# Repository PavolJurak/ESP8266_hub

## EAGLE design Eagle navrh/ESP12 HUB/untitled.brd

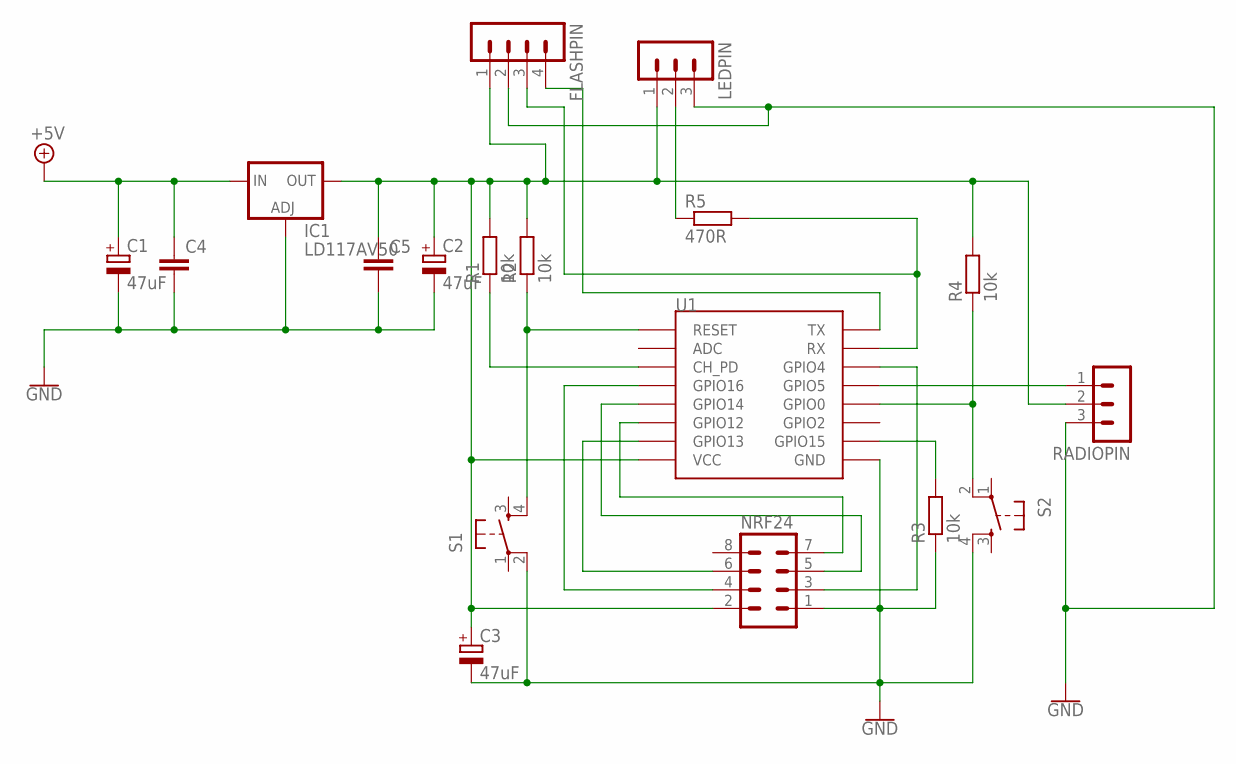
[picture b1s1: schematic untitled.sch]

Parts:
C1, C2, C3: 47uF; E2-5
C4, C5: C-EU025-025X050; C025-025X050
FLASHPIN: MA04-1
IC1: LD117AV50; TO220L1
LEDPIN: MA03-1
NRF24: MA04-2
R1, R2, R3, R4: 10k; 0207/10
R5: 470R; 0207/10
RADIOPIN: MA03-1
S1, S2: TAC_SWITCHPTH; TACTILE-PTH
U1: ESP12

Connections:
GND: C1.-, C2.-, C3.-, C4.2, C5.2, FLASHPIN.2, IC1.1 (ADJ), LEDPIN.3, NRF24.1, R3.1, RADIOPIN.3, S1.2, S2.4, U1.GND
unnamed: NRF24.6, U1.GPIO13
unnamed: R2.1, S1.4, U1.RESET
unnamed: R1.1, U1.CH_PD
unnamed: C2.+, C3.+, C5.1, FLASHPIN.1, IC1.2 (OUT), LEDPIN.1, NRF24.2, R1.2, R2.2, R4.2, RADIOPIN.2, U1.VCC
unnamed: R3.2, U1.GPIO15
unnamed: NRF24.7, U1.GPIO12
unnamed: NRF24.5, U1.GPIO14
unnamed: NRF24.3, U1.GPIO4
unnamed: NRF24.4, U1.GPIO16
unnamed: RADIOPIN.1, U1.GPIO5
unnamed: C1.+, C4.1, IC1.3 (IN)
unnamed: FLASHPIN.3, R5.2, U1.RX
unnamed: R4.1, S2.2, U1.GPIO0
unnamed: LEDPIN.2, R5.1
unnamed: FLASHPIN.4, U1.TX

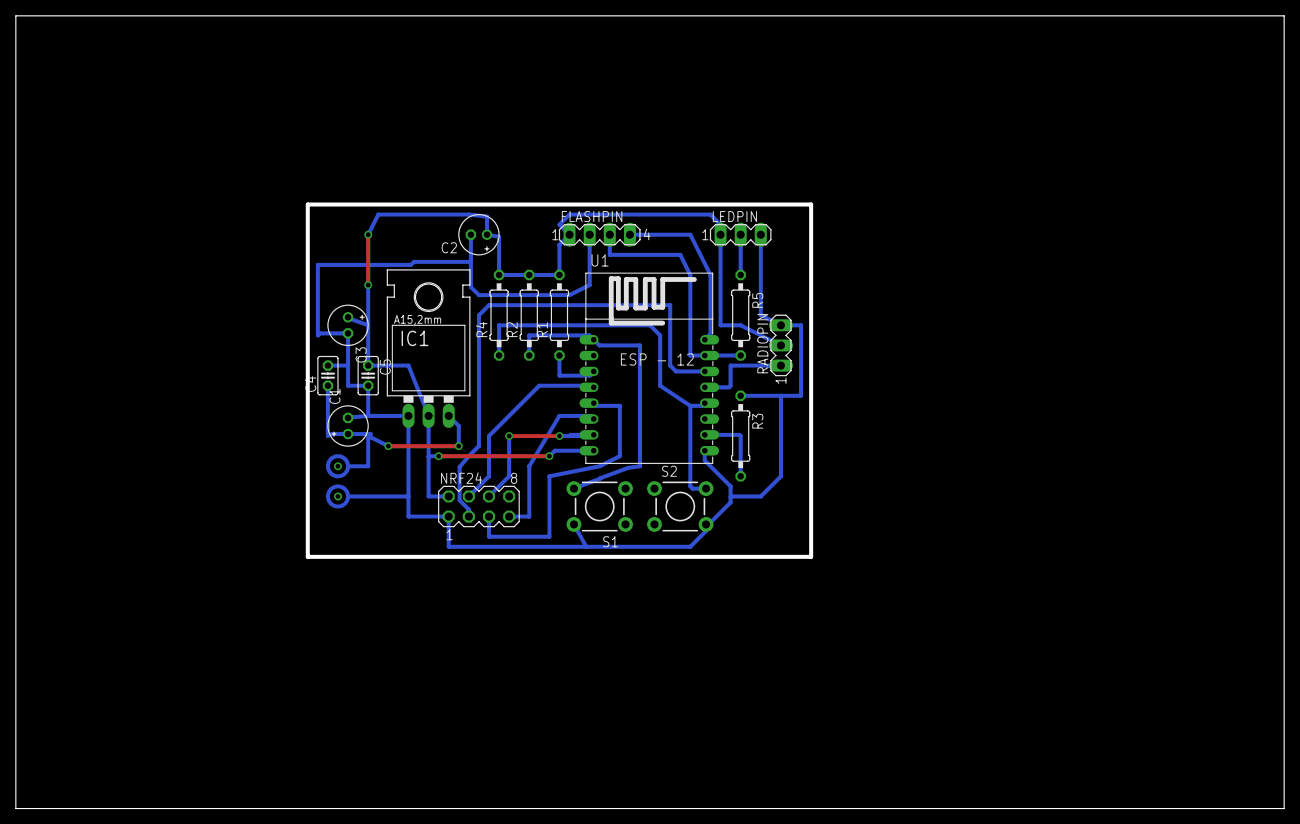
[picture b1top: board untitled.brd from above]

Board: 2 copper layers, 160.0 x 100.0 mm, 18 parts (0 on the bottom side), 16 nets.

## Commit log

2019-02-05 Version 1.0

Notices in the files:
parts and their libraries:
SparkFun-Retired: Licensing: Creative Commons ShareAlike 4.0 International - https://creativecommons.org/licenses/by-sa/4.0
